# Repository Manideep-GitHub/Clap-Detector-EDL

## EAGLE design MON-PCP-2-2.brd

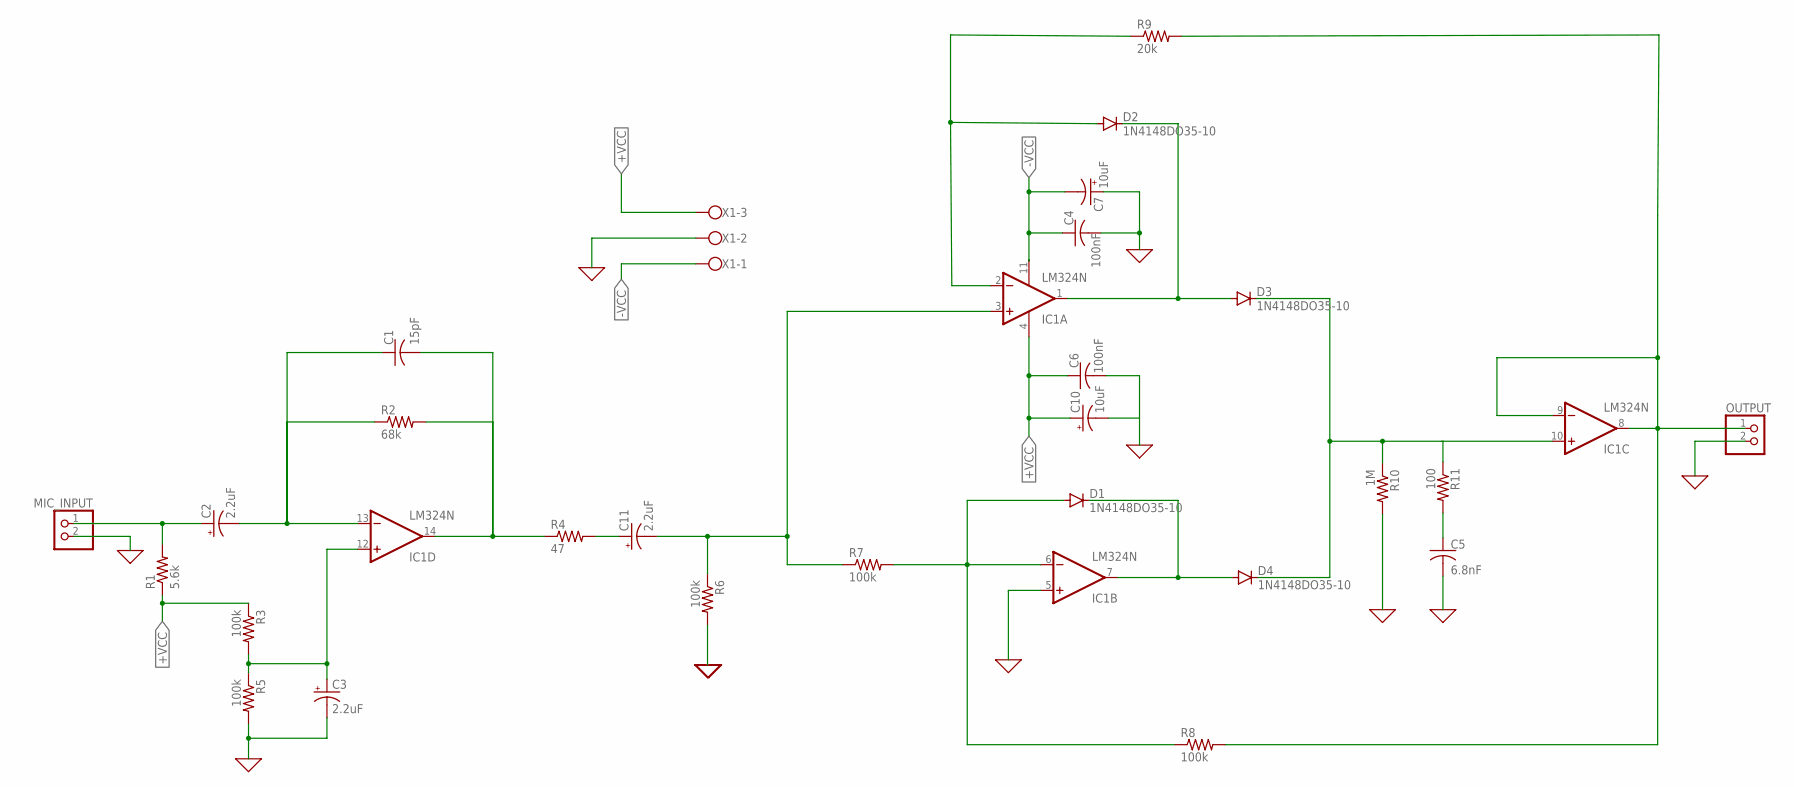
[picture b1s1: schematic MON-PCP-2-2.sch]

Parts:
C1: 15pF; C050-025X075
C2, C3, C11: 2.2uF; E2,5-7
C4, C6: 100nF; C050-025X075
C5: 6.8nF; C050-025X075
C7, C10: 10uF; E2,5-7
D1, D2, D3, D4: 1N4148DO35-10; DO35-10
IC1: LM324N; DIL14
MIC_INPUT: PINHD-1X2; 1X02
OUTPUT: PINHD-1X2; 1X02
R1: 5.6k; 0207/10
R2: 68k; 0207/10
R3, R5, R6, R7, R8: 100k; 0207/10
R4: 47; 0207/10
R9: 20k; 0207/10
R10: 1M; 0207/10
R11: 100; 0207/10
X1: W237-103

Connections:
0: C3.-, C4.2, C5.2, C6.2, C7.+, C10.-, IC1.5 (+IN), MIC_INPUT.2, OUTPUT.2, R5.2, R6.2, R10.2, X1.2
+VCC: C6.1, C10.+, IC1.4 (V+), R1.1, R3.1, X1.3
-VCC: C4.1, C7.-, IC1.11 (V-), X1.1
unnamed: D1.A, IC1.6 (-IN), R7.2, R8.1
unnamed: C3.+, IC1.12 (+IN), R3.2, R5.1
unnamed: C1.1, C2.-, IC1.13 (-IN), R2.1
unnamed: C11.+, R4.2
unnamed: C1.2, IC1.14 (OUT), R2.2, R4.1
unnamed: C11.-, IC1.3 (+IN), R6.1, R7.1
unnamed: D1.C, D4.A, IC1.7 (OUT)
unnamed: D2.C, D3.A, IC1.1 (OUT)
unnamed: D3.C, D4.C, IC1.10 (+IN), R10.1, R11.1
unnamed: C5.1, R11.2
unnamed: D2.A, IC1.2 (-IN), R9.1
VIN: C2.+, MIC_INPUT.1, R1.2
VOUT: IC1.8 (OUT), IC1.9 (-IN), OUTPUT.1, R8.2, R9.2

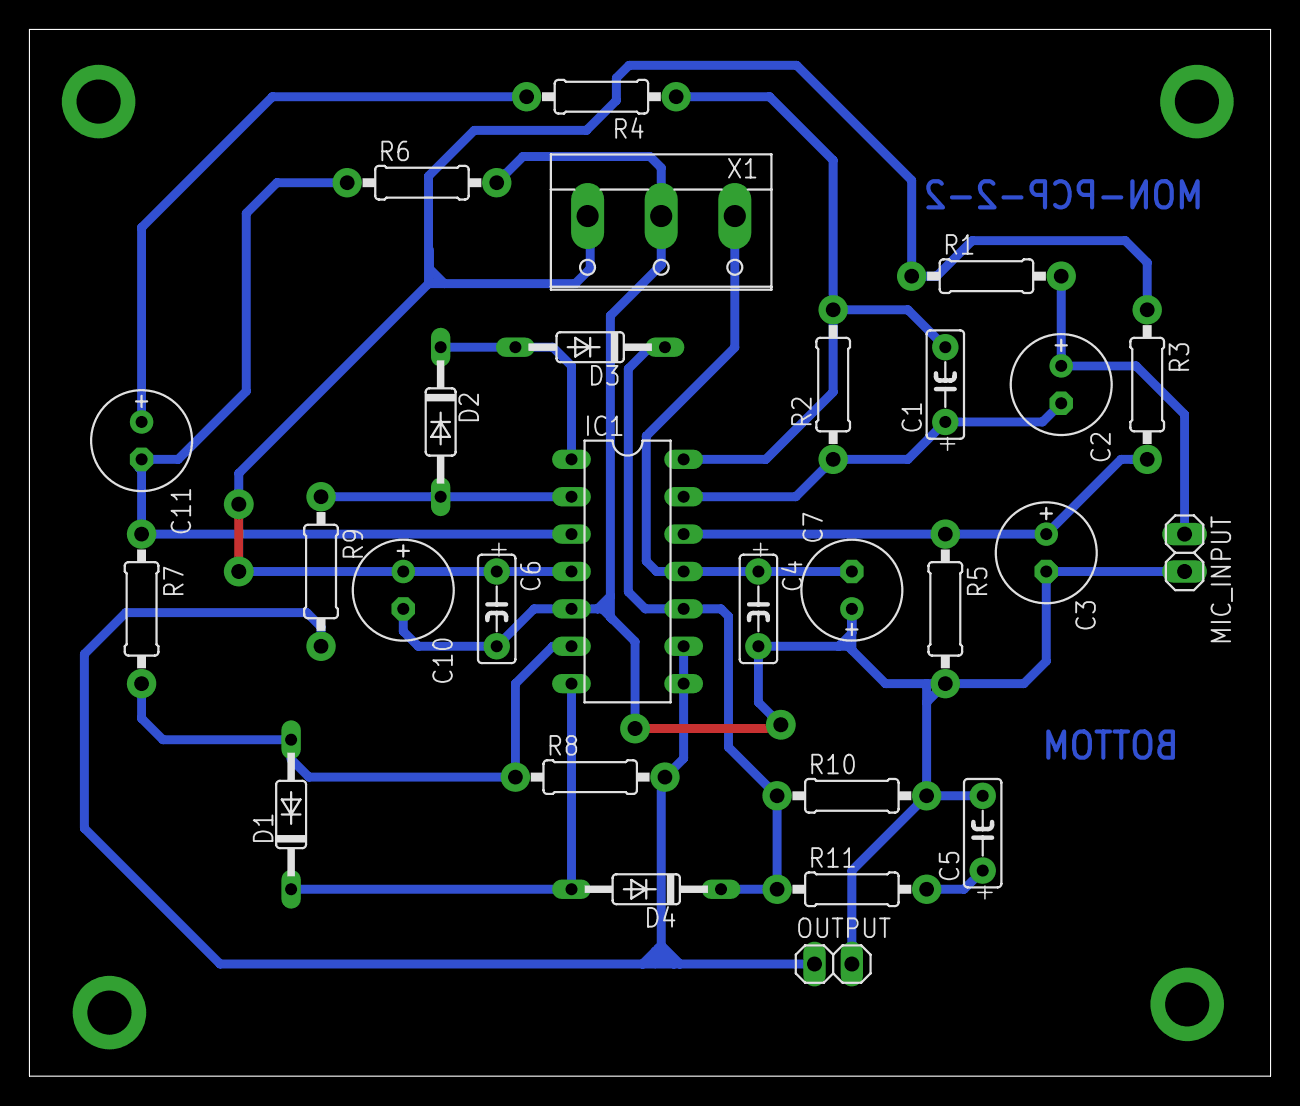
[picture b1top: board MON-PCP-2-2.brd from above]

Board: 2 copper layers, 84.3 x 71.1 mm, 28 parts (0 on the bottom side), 16 nets.
